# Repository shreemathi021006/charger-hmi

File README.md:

# Smart Adaptive Charger HMI — ESP32 + BLE/Bluetooth App Control

An intelligent, retrofit charger add-on that turns any existing certified AC‑DC
charger into a smart, app-controlled, adaptive charging system — without
modifying the charger itself or the device being charged.

Built for a project expo demo. The core idea: most "smart chargers" either
read the OS's own battery API *or* use external current sensing, rarely both,
and almost none offer a longevity-style target (e.g. "charge to 80% and
hold") on a retrofit external unit. This project combines live, phone-reported
battery percentage (ground truth) with independent current/voltage telemetry
(for monitoring, diagnostics, and a safety fallback) in a single compact HMI
unit.

---

## How it works (big picture)

```
230V AC
   |
   v
[Existing certified charger brick — UNMODIFIED]
   |
   v
19V DC output
   |
   v
[THIS UNIT — current/voltage sense, relay, HMI, Bluetooth]
   |
   v
Laptop / device DC input
```

The unit sits inline between an existing, already-certified charger and the
device being charged. It does **not** rebuild the AC-DC/flyback power stage —
that stays inside the sealed, certified brick, which keeps the whole build
safe to demo live with no exposed mains voltage. All of this project's
original engineering sits in the sensing, decision, and HMI layer.

---

## Features

- **Two charging modes**
  - **Default** — charges to a fixed target (80% by default), cutoff
    verified by the phone's real, live battery percentage.
  - **Manual** — user chooses either:
    - a custom **target percentage** (cutoff verified the same way), or
    - a custom **target time** (pure countdown timer, relay cuts off when
      the time elapses).
- **Real battery percentage, not a guess.** The connected phone reports its
  actual OS-level battery percentage over Bluetooth every ~30 seconds via a
  small MIT App Inventor app, and the ESP32 uses that as the source of truth
  for cutoff — rather than inferring state-of-charge from current alone,
  which breaks down under fast-charge protocols that negotiate voltage.
- **Independent current/voltage telemetry (INA226).** Tracked continuously
  for the on-device display and diagnostics, decoupled from the main cutoff
  decision so a sensor misread can't block (or falsely stop) a charge.
- **On-device HMI** — 0.96" I2C OLED display plus four physical buttons
  (Select / Enter / Increment / Decrement) for full menu navigation without
  needing the phone app open at all times.
- **Hard relay cutoff** — physically disconnects the charger output once the
  target is reached, rather than relying on a soft/software-only stop.
- **Two independent I2C buses** (ESP32's dual hardware I2C peripherals) so
  the OLED and the INA226 sensor don't contend for bus bandwidth or
  addressing.

---

## Hardware

| Component | Role | Notes |
|---|---|---|
| ESP32 Dev Board | Main controller | Built-in classic Bluetooth, dual I2C |
| 0.96" I2C OLED (SSD1306) | On-device display | 128x64, address `0x3C` |
| INA226 current/voltage sensor | Live telemetry | Address `0x44`, 0.1Ω shunt |
| Relay module | Hard cutoff switch | Switches the charger's DC output line |
| 4x push buttons | Local HMI input | Select, Enter, Increment, Decrement |
| Existing certified AC-DC charger | Power source | Unmodified, used as-is |

### Pin map

| Signal | ESP32 Pin |
|---|---|
| OLED SDA | GPIO 4 |
| OLED SCL | GPIO 13 |
| INA226 SDA | GPIO 21 |
| INA226 SCL | GPIO 22 |
| Button — Select | GPIO 16 |
| Button — Enter | GPIO 17 |
| Button — Increment | GPIO 18 |
| Button — Decrement | GPIO 19 |
| Relay control | GPIO 5 |

The OLED and INA226 are deliberately placed on **separate I2C buses**
(`Wire1` and `Wire` respectively) rather than shared, since the ESP32 has two
independent hardware I2C peripherals available.

---

## Software

### Firmware (`charger_hmi_oled.ino`)

- Arduino framework for ESP32.
- Libraries used:
  - `Adafruit_GFX` + `Adafruit_SSD1306` — OLED display driver
  - `INA226` (RobTillaart) — current/voltage sensor
  - `BluetoothSerial` — ESP32's built-in classic Bluetooth (no external
    Bluetooth module required)
- Menu system is a simple page-based state machine driven by the four
  buttons, mirroring a classic LCD-style 2-line UI (wrapped so it renders on
  the OLED through a small compatibility shim).
- The charging cutoff logic:
  - **Percentage-target modes** stop once the phone-reported battery
    percentage reaches the target.
  - **Time-target mode** stops on a plain elapsed-time countdown.
- INA226 readings (current in mA, voltage in V) are shown live on-screen at
  all times during a charging session, independent of which cutoff mode is
  active.

### Mobile app (MIT App Inventor)

- Reads the phone's real battery level using the **Taifun Battery Manager**
  extension (`puravidaapps.com/battery.php`).
- Pairs with the ESP32 over classic Bluetooth (device name `ESP32_MIT_APP`).
- A `Clock` component fires every 30 seconds, sending the current battery
  percentage as a plain text line (e.g. `"65\n"`) to the ESP32 over
  `BluetoothClient`.

---

## Setup

1. **Arduino IDE**: install the ESP32 board package, then install the
   `Adafruit SSD1306`, `Adafruit GFX`, and `INA226` (RobTillaart) libraries
   via Library Manager.
2. Flash `charger_hmi_oled.ino` to the ESP32.
3. **MIT App Inventor**: import the Taifun Battery Manager extension, add a
   `BluetoothClient`, a `Clock` (30000 ms interval), and wire up the
   Connect → Timer → Send blocks described in the firmware's companion
   notes.
4. Power the unit from the existing charger's 19V output (tapped inline,
   before the relay/output jack), pair the phone with `ESP32_MIT_APP`, and
   select a charging mode from the OLED menu.

---

## Safety notes

- The AC-DC/isolation stage is intentionally **not** rebuilt from scratch for
  this unit — it remains inside the original, certified charger brick. Only
  the already-isolated, low-voltage DC output is handled by this add-on.
- The relay provides a hard, physical cutoff independent of any software
  state, so a frozen or disconnected app/Bluetooth link does not leave the
  charger permanently energized in time-target mode (which uses a local
  timer regardless of connection state).

---

## Possible future improvements

- Fallback to INA226-based current-taper cutoff estimation if the phone's
  Bluetooth link drops during a percentage-target session (dual-verified
  cutoff).
- Session energy logging (Wh) and basic cost estimation using the INA226's
  continuous readings.
- Over-temperature / over-current protective cutoff, independent of the
  phone-reported percentage.
- Real-time clock (RTC) module for genuine "ready-by" scheduled charging.

---

## Project context

Built as a project-expo submission. Earlier design exploration covered a
full from-scratch AC-DC flyback power stage (UC3844 controller, MOSFET
selection, optocoupler/TL431 isolated feedback) for understanding the
underlying power electronics; the final build instead retrofits onto an
existing certified charger for safety and build-time reasons, concentrating
original engineering effort on the sensing, decision-making, and HMI layers
described above.

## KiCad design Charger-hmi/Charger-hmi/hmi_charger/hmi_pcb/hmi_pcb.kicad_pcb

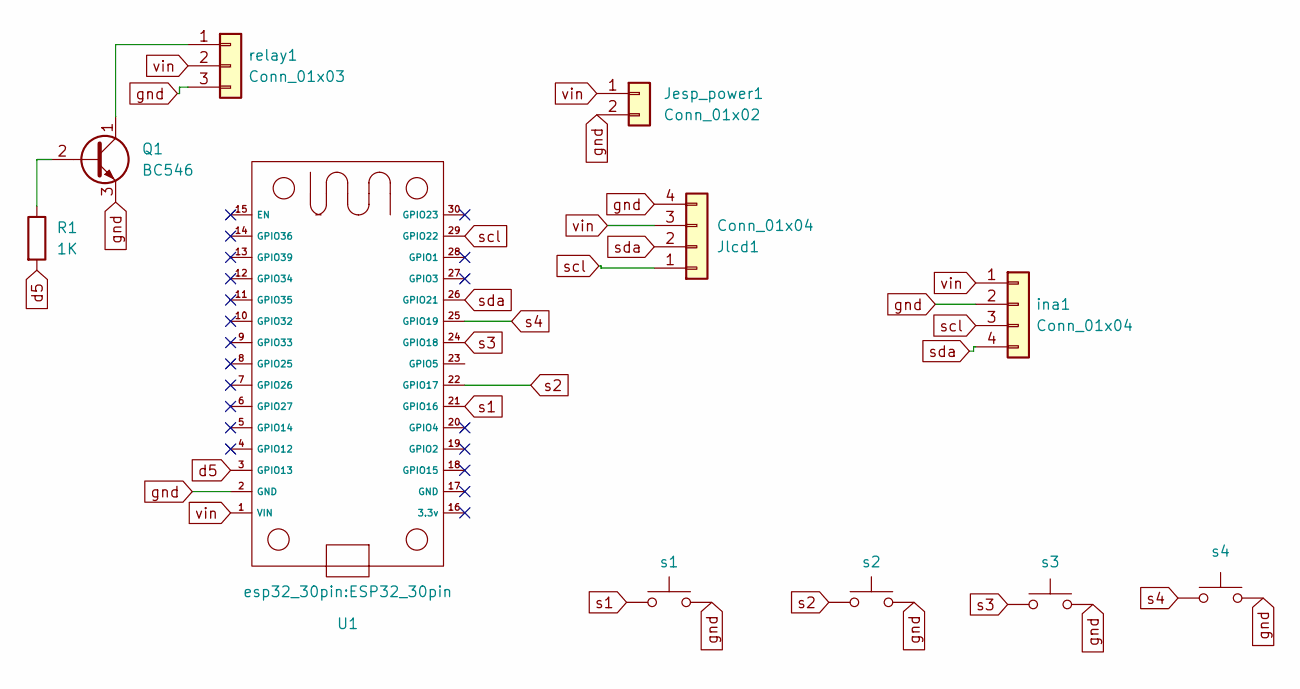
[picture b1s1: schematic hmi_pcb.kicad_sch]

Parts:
Jesp_power1: Conn_01x02; PinSocket_1x02_P2.54mm_Vertical
Jlcd1: Conn_01x04; PinSocket_1x04_P2.54mm_Vertical
Q1: BC546; TO-92_Inline
R1: 1K; R_Axial_DIN0207_L6.3mm_D2.5mm_P15.24mm_Horizontal
SW1: s1; SW_PUSH_6mm_H5mm
SW2: s2; SW_PUSH_6mm_H5mm
SW3: s3; SW_PUSH_6mm_H5mm
SW4: s4; SW_PUSH_6mm_H5mm
U1: ESP32_30pin
ina1: Conn_01x04; PinSocket_1x04_P2.54mm_Vertical
relay1: Conn_01x03; PinSocket_1x03_P2.54mm_Vertical

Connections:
unnamed: Q1.2 (B), R1.1
unnamed: Q1.1 (C), relay1.1
d5: R1.2, U1.3 (GPIO13)
gnd: Jesp_power1.2, Jlcd1.4, Q1.3 (E), SW1.2, SW2.2, SW3.2, SW4.2, U1.2 (GND), ina1.2, relay1.3
s1: SW1.1, U1.21 (GPIO16)
s2: SW2.1, U1.22 (GPIO17)
s3: SW3.1, U1.24 (GPIO18)
s4: SW4.1, U1.25 (GPIO19)
scl: Jlcd1.1, U1.29 (GPIO22), ina1.3
sda: Jlcd1.2, U1.26 (GPIO21), ina1.4
vin: Jesp_power1.1, Jlcd1.3, U1.1 (VIN), ina1.1, relay1.2

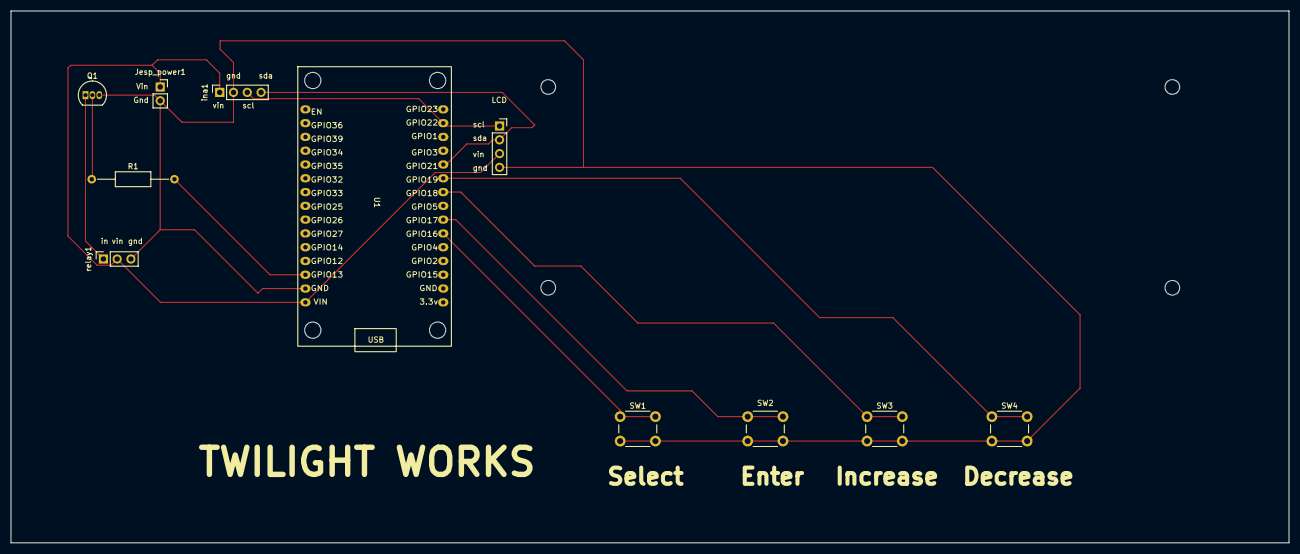
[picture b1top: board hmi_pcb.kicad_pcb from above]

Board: 2 copper layers, 235.5 x 98.0 mm, 11 parts (0 on the bottom side), 11 nets.
